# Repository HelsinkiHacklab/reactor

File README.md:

# A nuclear reactor simulator / game project, by [Helsinki Hacklab][hlab].

Uses physical consoles with buttons and gauges for input and output and a linux computer running various pieces of interfacing and simulation software.

Design and plans backups from etherpad here: http://helsinkihacklab.github.io/kirjoitusalusta_backups/hacklab-reactor.html

A phone-cam video of the first console & reactor lid in action: http://www.youtube.com/watch?v=7-S2qzXuEK0

# Exhibitions

## ALT Party 2011

We didn't quite finish everything in time but still got very nice feedback, photos at http://www.hacklab.fi/2011/10/alt-party-ohi-helsinki-yha-olemassa/ ([Google translated][1]), Jeri shot a video: http://www.youtube.com/watch?v=tjDI3drK0fk

[1]: http://translate.google.com/translate?sl=fi&tl=en&js=n&prev=_t&hl=en&ie=UTF-8&layout=2&eotf=1&u=http%3A%2F%2Fhelsinki.hacklab.fi%2F2011%2F10%2Falt-party-ohi-helsinki-yha-olemassa%2F

## Camp Pixelache 2012

The game was playable and we made a lot of alarm noises, the dials indicating control rod positions were missing though (we didn't have enough time to re-do them as most of the servos used at ALT party were dead).

Some photos from the event and late nights preceding it can be seen in this [article][2] (text in Finnish, [Google Translated][3])

[2]: http://www.mbnet.fi/artikkeli/blogit/mblabra/hacklabin_reaktoripeli_kotitekoinen_t_ernobyl
[3]: http://translate.google.com/translate?hl=en&sl=fi&tl=en&u=http%3A%2F%2Fwww.mbnet.fi%2Fartikkeli%2Fblogit%2Fmblabra%2Fhacklabin_reaktoripeli_kotitekoinen_t_ernobyl

## [WÄRK:fest][wark] 2012

We managed to get the control console to a mostly working state, also the reactor lid worked fine (apart from some minor glitches), even the smoke-machine controls worked (the smoke machine itself has to be
 repaired too, the pump-control triac had given up it's magic-smoke and had to be replaced).

"Pics or it didn't happen":

  * Rambo shot a very quick video with his cellphone: http://www.youtube.com/watch?v=7-S2qzXuEK0
  * Hamy shot a few pics: [lid](http://oh4kpn.1g.fi/kuvat/Demopartyt/WarkFest/2012/20121021-DSC_3592.jpg) & [console](http://oh4kpn.1g.fi/kuvat/Demopartyt/WarkFest/2012/20121021-DSC_3596.jpg)
  * YLE has a pic of [Rambo showing an air-core](http://img.yle.fi/uutiset/tekniikka/article6344340.ece/ALTERNATES/w960/warkfest_ydinreaktori_simulaattori.jpg) with the console on the background.
  * [Two reactor technicians at work](http://www.flickr.com/photos/ermuggo/8118672641/in/pool-2089172@N20) and [only slightly smoking reactor](http://www.flickr.com/photos/ermuggo/8118734690/in/pool-2089172@N20)

[wark]: http://www.warkfest.org/en/

## Model Expo 2013

Only the reactor control console was there.

## [FinnCon 2013][fc13]

The whole setup was there.

[fc13]: http://2013.finncon.org/

## Happy Hacking Day 2014

<http://happyhackingday.org/> as part of [Helsinki Hacklab][hlab]s stand. Full setup presented.

[hlab]: http://helsinki.hacklab.fi

## Model Expo 2014

Only the console was there, it still was a major attraction.

## Assembly (Summer) 2014

<http://hacklab.fi> was part of <http://puuhanurkka.fi> and the whole reactor setup was there, partycoded tweaks FTW. Pics:

  - <http://assembly.galleria.fi/kuvat/Assembly+Summer+2014/Tero+Heino/20140801_141203_THE_1616.jpg>
  - <http://assembly.galleria.fi/kuvat/Assembly+Summer+2014/Tuula+Ylikorpi/1A1C3810.jpg>
  - <http://assembly.galleria.fi/kuvat/Assembly+Summer+2014/Tuula+Ylikorpi/1A1C3808.jpg>
  - <http://assembly.galleria.fi/kuvat/Assembly+Summer+2014/Tuula+Ylikorpi/1A1C3514.jpg>
  - <http://assembly.galleria.fi/kuvat/Assembly+Summer+2014/Tuula+Ylikorpi/1A1C3389.jpg>
  - <http://assembly.galleria.fi/kuvat/Assembly+Summer+2014/Aleksi+Kinnunen/_V7Q6549.jpg>

There is also a [game review][pr14] (in Finnish), from the installation we had at ASM. The review-site aims to provide reviews for helping parents decide if a game is suitable for their children to play)

[pr14]: http://www.peliraati.fi/pelien-arvioinnit-mainmenu-27/pelit-7-mainmenu-44/669-reactor-simulator

## CCCamp 2015

Barely any photos of the reactor itself, [this one](https://www.flickr.com/photos/helsinkihacklab/20517571046/in/album-72157656773699850/) shows part of the control console and [this](https://www.flickr.com/photos/helsinkihacklab/20706549795/in/album-72157656974072878/) some moody smoke. But check out the following galleries from the camp in general:

  - <https://www.flickr.com/photos/helsinkihacklab/sets/72157657182416991>
  - <https://www.flickr.com/photos/helsinkihacklab/sets/72157656773699850>
  - <https://www.flickr.com/photos/helsinkihacklab/sets/72157656803571519>
  - <https://www.flickr.com/photos/helsinkihacklab/sets/72157656974072878>
  - <https://www.flickr.com/photos/helsinkihacklab/sets/72157657451044962>
  - <https://www.flickr.com/photos/helsinkihacklab/sets/72157657064568938>

## Vectorama 2022

Full set, the reactor-lid has some issues registering stomps and [overhaul][todofix]
is needed.

  - <https://kuvat.vectorama.info/kuvat/Vectorama+2022/9.6.2022+Torstai/mikaelpeltomaa_09-06-22_DSC04147.jpg> (scroll forward for a few more)
  - <https://kuvat.vectorama.info/kuvat/Vectorama+2022/9.6.2022+Torstai/EmmiHalmela-vectorama22-6192.jpg>
  - <https://kuvat.vectorama.info/kuvat/Vectorama+2022/10.6.2022+Perjantai/mikaelpeltomaa_10-06-22_DSC04667.jpg>
  - <https://kuvat.vectorama.info/kuvat/Vectorama+2022/11.6.2022+Lauantai/EmmiHalmela-vectorama22-7755.jpg>
  - <https://kuvat.vectorama.info/kuvat/Vectorama+2022/12.6.2022+Sunnuntai/mikaelpeltomaa_12-06-22_DSC06002.jpg> most of this load is directly related to the reactor.

[todofix]: https://github.com/HelsinkiHacklab/reactor/wiki/TODO#necessary-fixes

## Next up

ASM Summer 2022, lets see how many things we get fixed for that.

## After that: ???

Don't know yet, lets see if at some point we will get around to making the [coms-console][coms_jeri] functional too and/or the plant-control console, seen as the rightmost console on the coms-picture)

[coms_jeri]: http://helsinki.hacklab.fi/wp-content/uploads/2011/10/CIMG7885.jpg

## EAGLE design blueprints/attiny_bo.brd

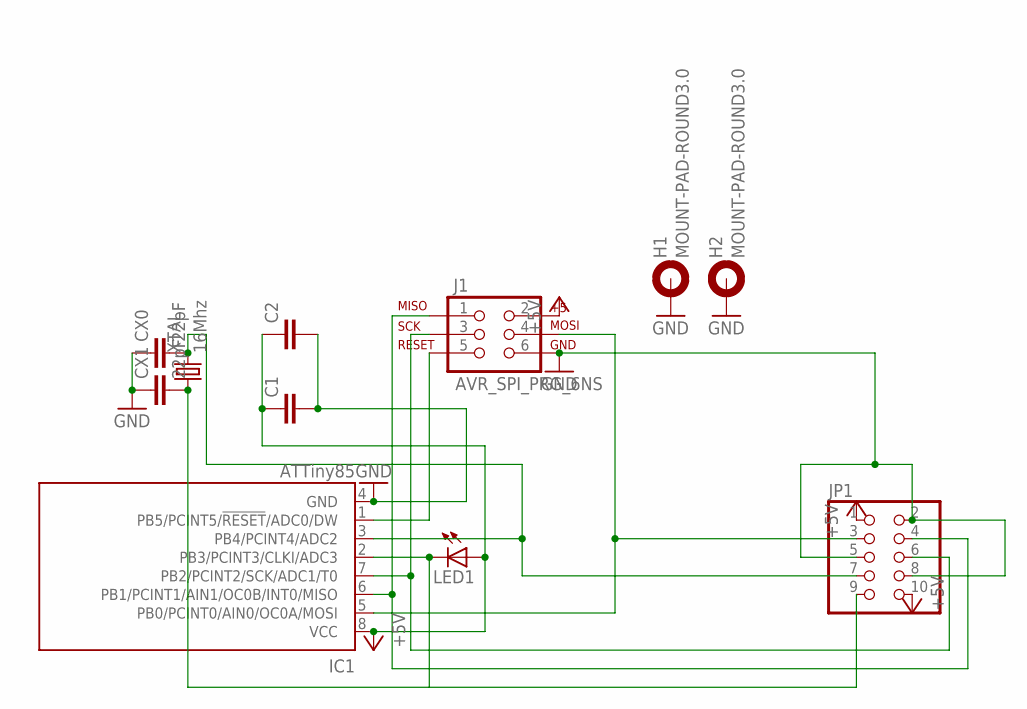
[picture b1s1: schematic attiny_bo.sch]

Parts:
C1, C2: C-EUC0805; C0805
CX0, CX1: 22pF; C0603
H1, H2: MOUNT-PAD-ROUND3.0; 3,0-PAD
IC1: ATTiny85; 8S2
J1: AVR_SPI_PRG_6NS; 2X3-NS
JP1: PINHD-2X5; 2X05
LED1: LED0603; LED-0603
XTAL: 16Mhz; CTS406

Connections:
+5V: C1.1, C2.1, IC1.8 (VCC), J1.2, JP1.1, JP1.10, LED1.A
GND: C1.2, C2.2, CX0.1, CX1.1, H1.B3,0, H2.B3,0, IC1.4 (GND), J1.6, JP1.2, JP1.5, JP1.8
PB0: IC1.5 (PB0/PCINT0/AIN0/OC0A/MOSI), J1.4, JP1.3
PB1: IC1.6 (PB1/PCINT1/AIN1/OC0B/INT0/MISO), J1.1, JP1.4
PB2: IC1.7 (PB2/PCINT2/SCK/ADC1/T0), J1.3, JP1.6
PB3: CX1.2, IC1.2 (PB3/PCINT3/CLKI/ADC3), JP1.9, LED1.C, XTAL.1; also elsewhere on the board
PB4: CX0.2, IC1.3 (PB4/PCINT4/ADC2), JP1.7, XTAL.3 (2); also elsewhere on the board
PB5: IC1.1 (PB5/PCINT5/!RESET!/ADC0/DW), J1.5

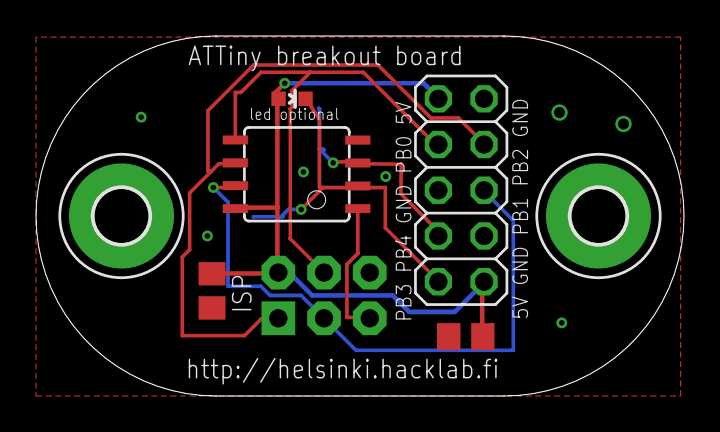
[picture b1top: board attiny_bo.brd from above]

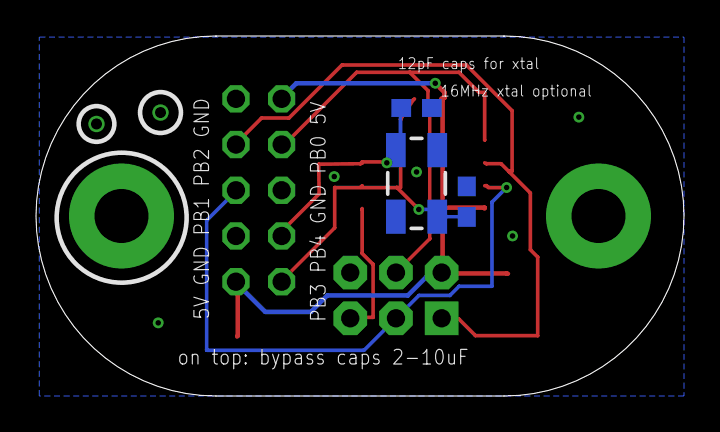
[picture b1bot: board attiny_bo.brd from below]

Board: 2 copper layers, 36.0 x 20.0 mm, 11 parts (3 on the bottom side), 8 nets.

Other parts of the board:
Y1: 16MHz; CRYSTAL-SMD-5X3

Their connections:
PB3: Y1.1; also elsewhere on the board
PB4: Y1.3; also elsewhere on the board

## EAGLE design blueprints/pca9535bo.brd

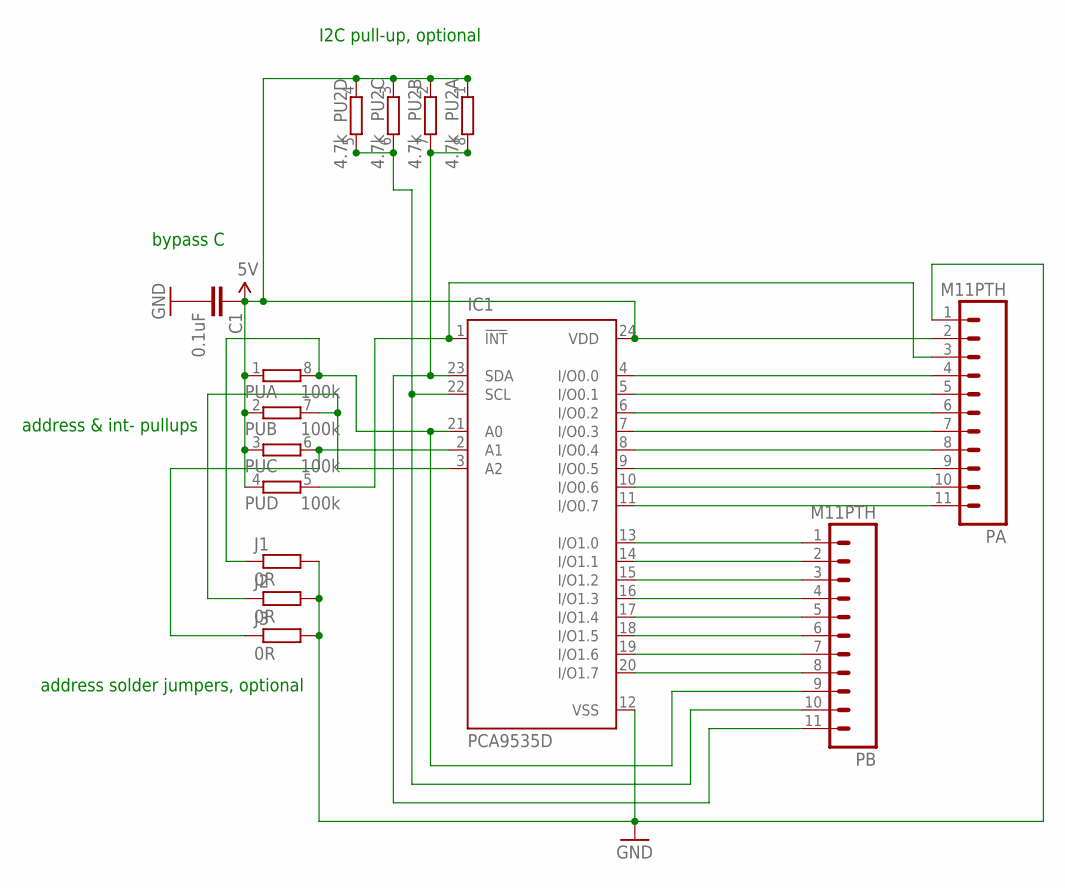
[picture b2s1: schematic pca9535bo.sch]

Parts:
C1: 0.1uF; C0805K
IC1: PCA9535D; SO24
J1, J2, J3: 0R; R0603
PA: M11PTH; 1X11
PB: M11PTH; 1X11
PU: 100k; CAY16
PU2: 4.7k; CAY16

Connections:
5V: C1.1, IC1.24 (VDD), PA.2, PU.1, PU.2 (1), PU.3 (1), PU.4 (1), PU2.1, PU2.2 (1), PU2.3 (1), PU2.4 (1)
A0: IC1.21 (A0), J1.1, PB.9, PU.8 (2)
A1: IC1.2 (A1), J3.1, PU.6 (2)
A2: IC1.3 (A2), J2.1, PU.7 (2)
GND: C1.2, IC1.12 (VSS), J1.2, J2.2, J3.2, PA.1
INT-: IC1.1 (!INT), PA.3, PU.5 (2)
PA0: IC1.4 (I/O0.0), PA.4
PA1: IC1.5 (I/O0.1), PA.5
PA2: IC1.6 (I/O0.2), PA.6
PA3: IC1.7 (I/O0.3), PA.7
PA4: IC1.8 (I/O0.4), PA.8
PA5: IC1.9 (I/O0.5), PA.9
PA6: IC1.10 (I/O0.6), PA.10
PA7: IC1.11 (I/O0.7), PA.11
PB0: IC1.13 (I/O1.0), PB.1
PB1: IC1.14 (I/O1.1), PB.2
PB2: IC1.15 (I/O1.2), PB.3
PB3: IC1.16 (I/O1.3), PB.4
PB4: IC1.17 (I/O1.4), PB.5
PB5: IC1.18 (I/O1.5), PB.6
PB6: IC1.19 (I/O1.6), PB.7
PB7: IC1.20 (I/O1.7), PB.8
SCL: IC1.22 (SCL), PB.10, PU2.5 (2), PU2.6 (2)
SDA: IC1.23 (SDA), PB.11, PU2.7 (2), PU2.8 (2)

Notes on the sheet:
I2C pull-up, optional
address solder jumpers, optional
address & int- pullups
bypass C

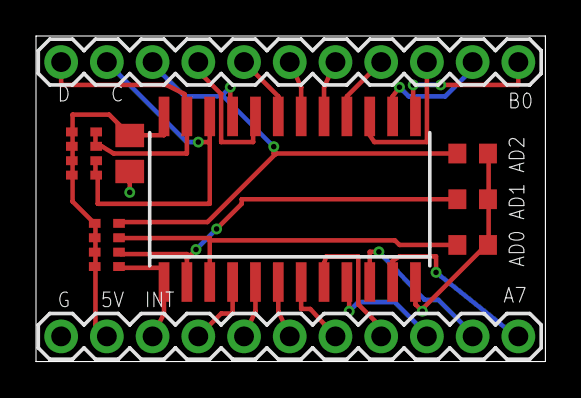
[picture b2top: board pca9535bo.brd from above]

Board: 2 copper layers, 28.3 x 18.1 mm, 9 parts (0 on the bottom side), 24 nets.

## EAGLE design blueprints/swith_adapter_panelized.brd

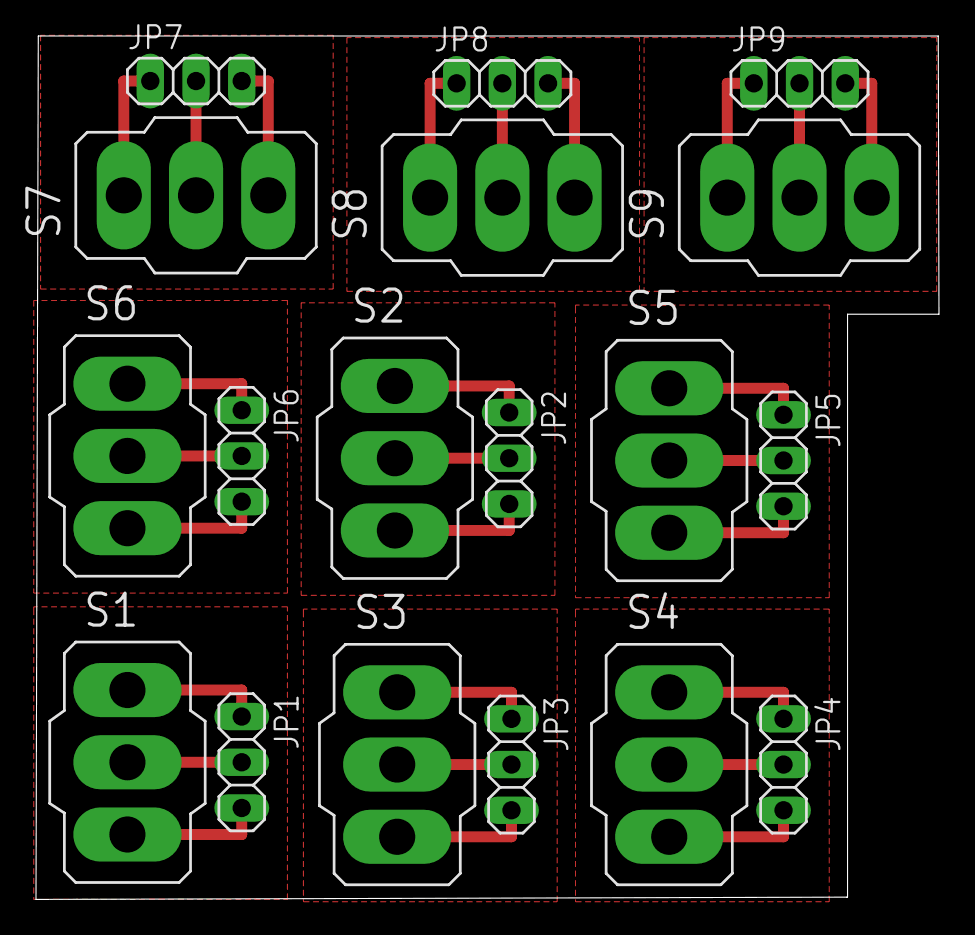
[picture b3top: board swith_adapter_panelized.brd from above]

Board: 2 copper layers, 50.2 x 48.0 mm, 18 parts (0 on the bottom side), 27 nets.

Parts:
JP1, JP2, JP3, JP4, JP5, JP6, JP7, JP8, JP9: 1X03
S1, S2, S3, S4, S5, S6, S7, S8, S9: 320-916

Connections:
unnamed: JP1.2, S1.2
unnamed: JP1.1, S1.1
unnamed: JP1.3, S1.3
unnamed: JP2.2, S2.2
unnamed: JP2.1, S2.1
unnamed: JP2.3, S2.3
unnamed: JP3.2, S3.2
unnamed: JP3.1, S3.1
unnamed: JP3.3, S3.3
unnamed: JP4.2, S4.2
unnamed: JP4.1, S4.1
unnamed: JP4.3, S4.3
unnamed: JP5.2, S5.2
unnamed: JP5.1, S5.1
unnamed: JP5.3, S5.3
unnamed: JP6.2, S6.2
unnamed: JP6.1, S6.1
unnamed: JP6.3, S6.3
unnamed: JP7.2, S7.2
unnamed: JP7.1, S7.1
unnamed: JP7.3, S7.3
unnamed: JP8.2, S8.2
unnamed: JP8.1, S8.1
unnamed: JP8.3, S8.3
unnamed: JP9.2, S9.2
unnamed: JP9.1, S9.1
unnamed: JP9.3, S9.3

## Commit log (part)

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2012-03-31 forgot the indices need to be listed like this
2012-03-31 dependencies and running instructions
2012-03-31 Started working on a component based plant simulator.
2012-03-31 simple shell script to fire up the whole stack while we do not have DBUS activation to do it for us
2012-03-31 helper script for launching everything and fix launching via path
2012-03-31 fix copy-paste leftover
2012-03-31 exit cleanly
2012-03-31 clean signal handling, there is only one proper way to launch this
2012-03-31 the ping <> rod coordinates mapping is still totally wacky but now I see the effect of a stomp in visualizer
2012-03-31 minor cleanup
2012-04-01 Testcommit.
2012-04-01 Working on plant sim.
2012-04-01 tried changing names but it does not help, it seems these QML pieces block any other ones started after them from being called
2012-04-01 the names need to match QML I forgot
2012-04-01 it seems we must not try to claim interface names that are already claimed, on the dbus-monitor at least we can still emit using "reserved" interface name but for some reason my simple test receiver 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
2012-04-01 added a note
2012-04-01 minor robustness improvements
2012-04-01 avoid calling servo moves if they would not actually move, this makes things much more reponsive is all servos are not actually moving
2012-04-01 experiment with processing these calculations in threads
2012-04-01 Revert "Revert "background the set_servo call (in fact the whole position interpolate etc should be backgrounded""
    This reverts commit 1cd9c64a48f30c33f52a4c52d9faab3bae05f199.
2012-04-01 implement the rod movement methods
2012-04-01 implement rod control in middleware
2012-04-01 the led gauges in theory work
2012-04-02 I2C pullups and sizing down
2012-04-02 two polygons at least was a bad idea
2012-04-02 forgot some junction
2012-04-02 GND polygon at bottom works
2012-04-02 cleaned up
2012-04-02 silkscreen improvements
2012-04-04 Shell script for installing most dependencies (python libs).
2012-04-07 Fluid simulation piping done, missing actual physical calculations.
2012-04-08 Ports now stored in fluid, updated fluid to support infinite liquid or gas (outdoors/river).
2012-04-08 Some debugging.
2012-04-09 Named fluid containers, worked on simulation.
2012-04-09 Some more reporting, trying to figure out pressures and flows.
2012-04-28 testing the led wiring, using buttton to switch which led should be on
2012-04-29 these mode settings work the same way as BusPirate
2012-04-30 use the new library support for the SPI clock speed
2012-04-30 initial support for PCA9535 as input, only tested with one board for now
2012-04-30 note about source of library used
2012-04-30 untested pca9535 bit output code
2012-05-01 name more descriptive of the use
2012-05-05 moved to YAML config files and added pin mappings and aliases
2012-05-05 working on the sketch code generator
2012-05-05 adding more support for features
2012-05-05 testing generated code
2012-05-05 add initialization message in so we can identify a board sooner
2012-05-05 shorter sleep for reset
2012-05-05 testing the recognizer
2012-05-05 trying to make things a bit more robust
2012-05-06 config normalization w regards to aliases, testing aliases
2012-05-06 dummy aliases for all pins for easier identification (the index reports are a bit iffy for that)
2012-05-06 fixed the short, verified one broken switch
2012-05-06 start adapting for aliased signals
2012-05-06 gauge code talks to board but seems mapping is a bit off still
2012-05-06 correct order of leds in gauges, make neutrons autoranging
2012-05-07 initial mappings for generating the code for the arduino used to communicate with the reactor lid
2012-05-07 new submodule
2012-05-07 trying to do this submodule song & dance properly this time
2012-05-07 cleaning up some old stuff
2012-05-07 also not needed
2012-05-07 use less CPU, 20FPS is more than enough
2012-05-07 switched to call_cached
2012-05-08 more input pins
2012-05-08 rewired the missing signal, it seems pin51 is broken on the mega1280 we use
2012-05-08 change signal names to match middleware.py
2012-05-10 adding some simple loops and middleware supports for some related simulation signals
2012-05-10 configure flux range, cancel the other alarm loops on blowout
2012-05-10 test show 250ms is a good interval
2012-05-10 blink rod top light if it has cells in danger of melting
2012-05-10 do not allow restaring blink loops
2012-05-10 methods for resetting the led states
2012-05-10 experiments
2012-05-12 these settings seem pretty ok, need to find a mosfet for the speaker, the "too big" BJT seems not to be saturated by our puny little uc
2012-05-12 slow down I2C speed since we have long bus, fix a typo in blink logic
2012-05-12 adding support for aircores
2012-05-12 basic support for the aircore I2C api
2012-05-12 missed some rather critical pieces
2012-05-12 found these rather goos sound laying around on the hacknad, why no-one added them here ??
2012-05-12 adding concept art before it is lost
2012-05-12 some concept art files missed by previous add
2012-05-21 pixelache is over
2012-05-22 fix sleep-deprivation induced stupidity
2012-05-23 linked to article with photos from Pixelache
2012-05-23 untested code to launch the stack with physical consoles
2012-05-23 window titles and since we depend already on gnome-termninal specific feature do not bother configureing the terminal prog
2012-05-23 make the launcher runnable via desktop links
2012-05-26 this method is universally usefull so make it part of the libs
2012-05-26 QT stub imports
2012-07-08 Added Jeris video and GTranslate links
2012-07-31 simple breakout for attiny with ISP and 2x5 breakout header with pins in port order
2012-07-31 first autorouted version, board can be made smaller and needs some mounting holes etc
2012-07-31 use wider traces for 5v and gnd
2012-08-01 make the board pill-shaped
2012-08-01 added some labels and realized I need to re-arrange the signals on the 5x2 header since we do not want PB5 aka reset there (those who need it can get it from the ISP header)
2012-08-01 rethought the signals to 5x2 header, tuned the mounting pad positions
2012-08-01 smaller isolation on polygons, minor routing adjustments
2012-08-01 DRC fixes
2012-08-02 started adding optional crystal to the board
2012-08-02 switched to smaller and better available cxtal
2012-08-02 approve inconsequential DRC errors
2012-08-07 scanning the kb matrix
2012-08-07 making a sketch for the 7x7 kb matrix that emulates the straight digital pins of the reactor lid arduino mega
2012-08-07 minor fixes, now seems to work
2012-08-07 the matrix indices got flipped
2012-08-12 corrected comments
2012-08-12 the diagram when using one of my attiny breakouts (stuff on the board [like ISP header, bypass cap etc] not pictured, also the footprint is slightly wider)
2012-08-12 note about optional cap on 7505 output
2012-08-12 minor clarification
2012-08-12 only one h1 level heading
2012-08-13 switch to flash strings: gsed -i -r -e "s%Serial.print(ln)?\\((\".*?\")\\)%Serial.print\1(F(\2))%g"
2012-08-14 simple adapter for the panel switches to standard pin headers
2012-08-14 moved to new repo
2012-08-20 Work on showing rod positions in visualizer. Does not yet work.
2012-10-01 started designing the enclosure for the mini reactor lid
2012-10-01 sometimes it is a good idea to read the manual, this is much more elegant way
2012-10-01 visualize the actual pcb as well, this way found a problem in my previous roundedsq version
2012-10-01 holes only on the rod positions
2012-10-01 slightly better hole size and placement
2012-10-01 some comments
2012-10-01 DXF exports of the current version
2012-10-02 the omit hole for the mwells
2012-10-02 screw holes (4mm)
2012-10-02 the initial layer is no longer needed
2012-10-02 export as 1000dpi for lasercutter
2012-10-02 the button pitch is slightly less than 20mm
2012-10-03 exported for lasercutter
2012-10-11 added a todo
2012-10-11 better variable names
2012-10-11 aw fuu, it is caused by this http://code.google.com/p/arduino-tiny/issues/detail?id=58
2012-10-11 this still works
2012-10-11 almost there, but how to shrink the code a bit ? to avoid the linker bug that prevents me from using full code size
2012-10-11 regorg the displays so the match the power-rail layout
2012-10-11 better variable names but I just realized I need to do the mA conversions too..
2012-10-11 implemented the use of the mv->ma conversion functions and ran into code-size bug again, so manually implemented the number formatter for my special case
2012-10-11 forgot that amps can be >9 and with the fixed linker sprintf is no longer a dealbreaker
2012-10-12 float version to track source of some voltage errors
2012-10-12 cleanup and restore the current sensor mV->mA calculations
2012-10-13 drew up the schematic
2012-10-13 fixes and tunings
2012-10-14 the backlight needs resistor afterall, it just is a very small one when compared to led resistors in general
2012-10-14 new sounds from dta
2012-10-14 mappings
2012-10-14 mappings and adjustments
2012-10-14 rotate&mirrot the fake lid so now is used in "portrait" mode
2012-10-21 the old servo map is useless
2012-10-21 wark adjustments, loop limit, configurable sink (use pulse)
2012-10-21 disable the rod samples again
2012-10-21 restore the zero p for hit when rod in place
2012-10-23 wark is over, added some links to pics & video
2012-10-25 link to the image, the lightbox does not work with direct links
2013-01-12 stub
2013-01-12 numbers maps
2013-01-12 the map is usable(enough) now
2013-01-12 note some string patterns
2013-04-25 started writing ardubus wrapper for the trivial I2C ASCII display
2013-04-25 untested code generator for I2C ASCII arDuBUS
2013-04-25 typecasting and new generated code (untested)
2013-04-26 UNTESTED add DBUS service method for the i2cascii (mwdisplay) stuff
2013-04-27 we need to pass the address to make the pointer work correctly
2013-05-05 the submodules were a bad idea afterall
2013-05-18 first step...
2013-05-18 Extremely simple pubsub-test for zmq playground
2013-05-18 random port binding example and configurable sub connect port
2013-05-18 use ioloop for timing the sends
2013-05-18 Added some example data and topic handling
2013-05-18 Create virtualenv instructions
2013-05-18 Added DNSService fd processing to ioloop.
2013-05-18 Added pybonjour to random_port
2013-05-18 pybonjour needs this library
2013-05-18 pybonjour is available via pip
2013-05-18 Fixed pub_test bonjour stuff so that it works
2013-05-18 service resolving example
2013-05-18 fix the random port version
2013-05-18 except it seems the callback is not called for the pub_test.py case ??, anyway detabbed the line
2013-05-18 forgot to copy the correct type def from pub_example
2013-05-18 Fixed conflicts.
2013-05-18 tuned settings for raspi and the BW monitor in the coms-console
2013-05-18 put the resolver to our utilities library
2013-05-18 avoid unneeded conversions
2013-05-18 move the bonjour service reg to helper module
2013-05-19 working on wrappers and decorators
2013-05-19 we will have a connect wrapper as well...
2013-05-19 helpers for topic callbacks
2013-05-19 reset these properties on reconnect
2013-05-19 merging
2013-05-19 testing audio for a while
2013-05-19 simple async server/client pattern
2013-05-19 router/dealer with bonjour service discovery and random port binding
2013-05-19 rewrite the server to use the utilities for port binding
2013-05-19 change the pubsub decorator name to be more clear when we have rpc methods as well
2013-05-19 remove unused code
2013-05-19 method decorator
2013-05-19 async call helper
2013-05-19 the other way would be to get the wrapper for registering callbacks initially via the ct instance from the module
2013-07-07 glob the comport paths
2014-01-31 these have been moved to https://github.com/rambo/python-zmqdecorators
2014-01-31 note that the lib has been moved
2014-02-08 use two configs
2014-02-08 sound files from the mac
2014-02-08 the mac checkout
2014-02-08 try to ignore vi backup files
2014-03-25 HHD came and went
2014-08-01 adjust params
2014-08-01 even dimmer
2014-08-03 ASM2014
2014-11-30 added a review
2015-08-12 forot mwdisplasy hopme
2015-08-13 dbus updates the display, yeah!

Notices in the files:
parts and their libraries:
SparkFun-Connectors: Licensing: CC v3.0 Share-Alike You are welcome to use this library for commercial purposes.
